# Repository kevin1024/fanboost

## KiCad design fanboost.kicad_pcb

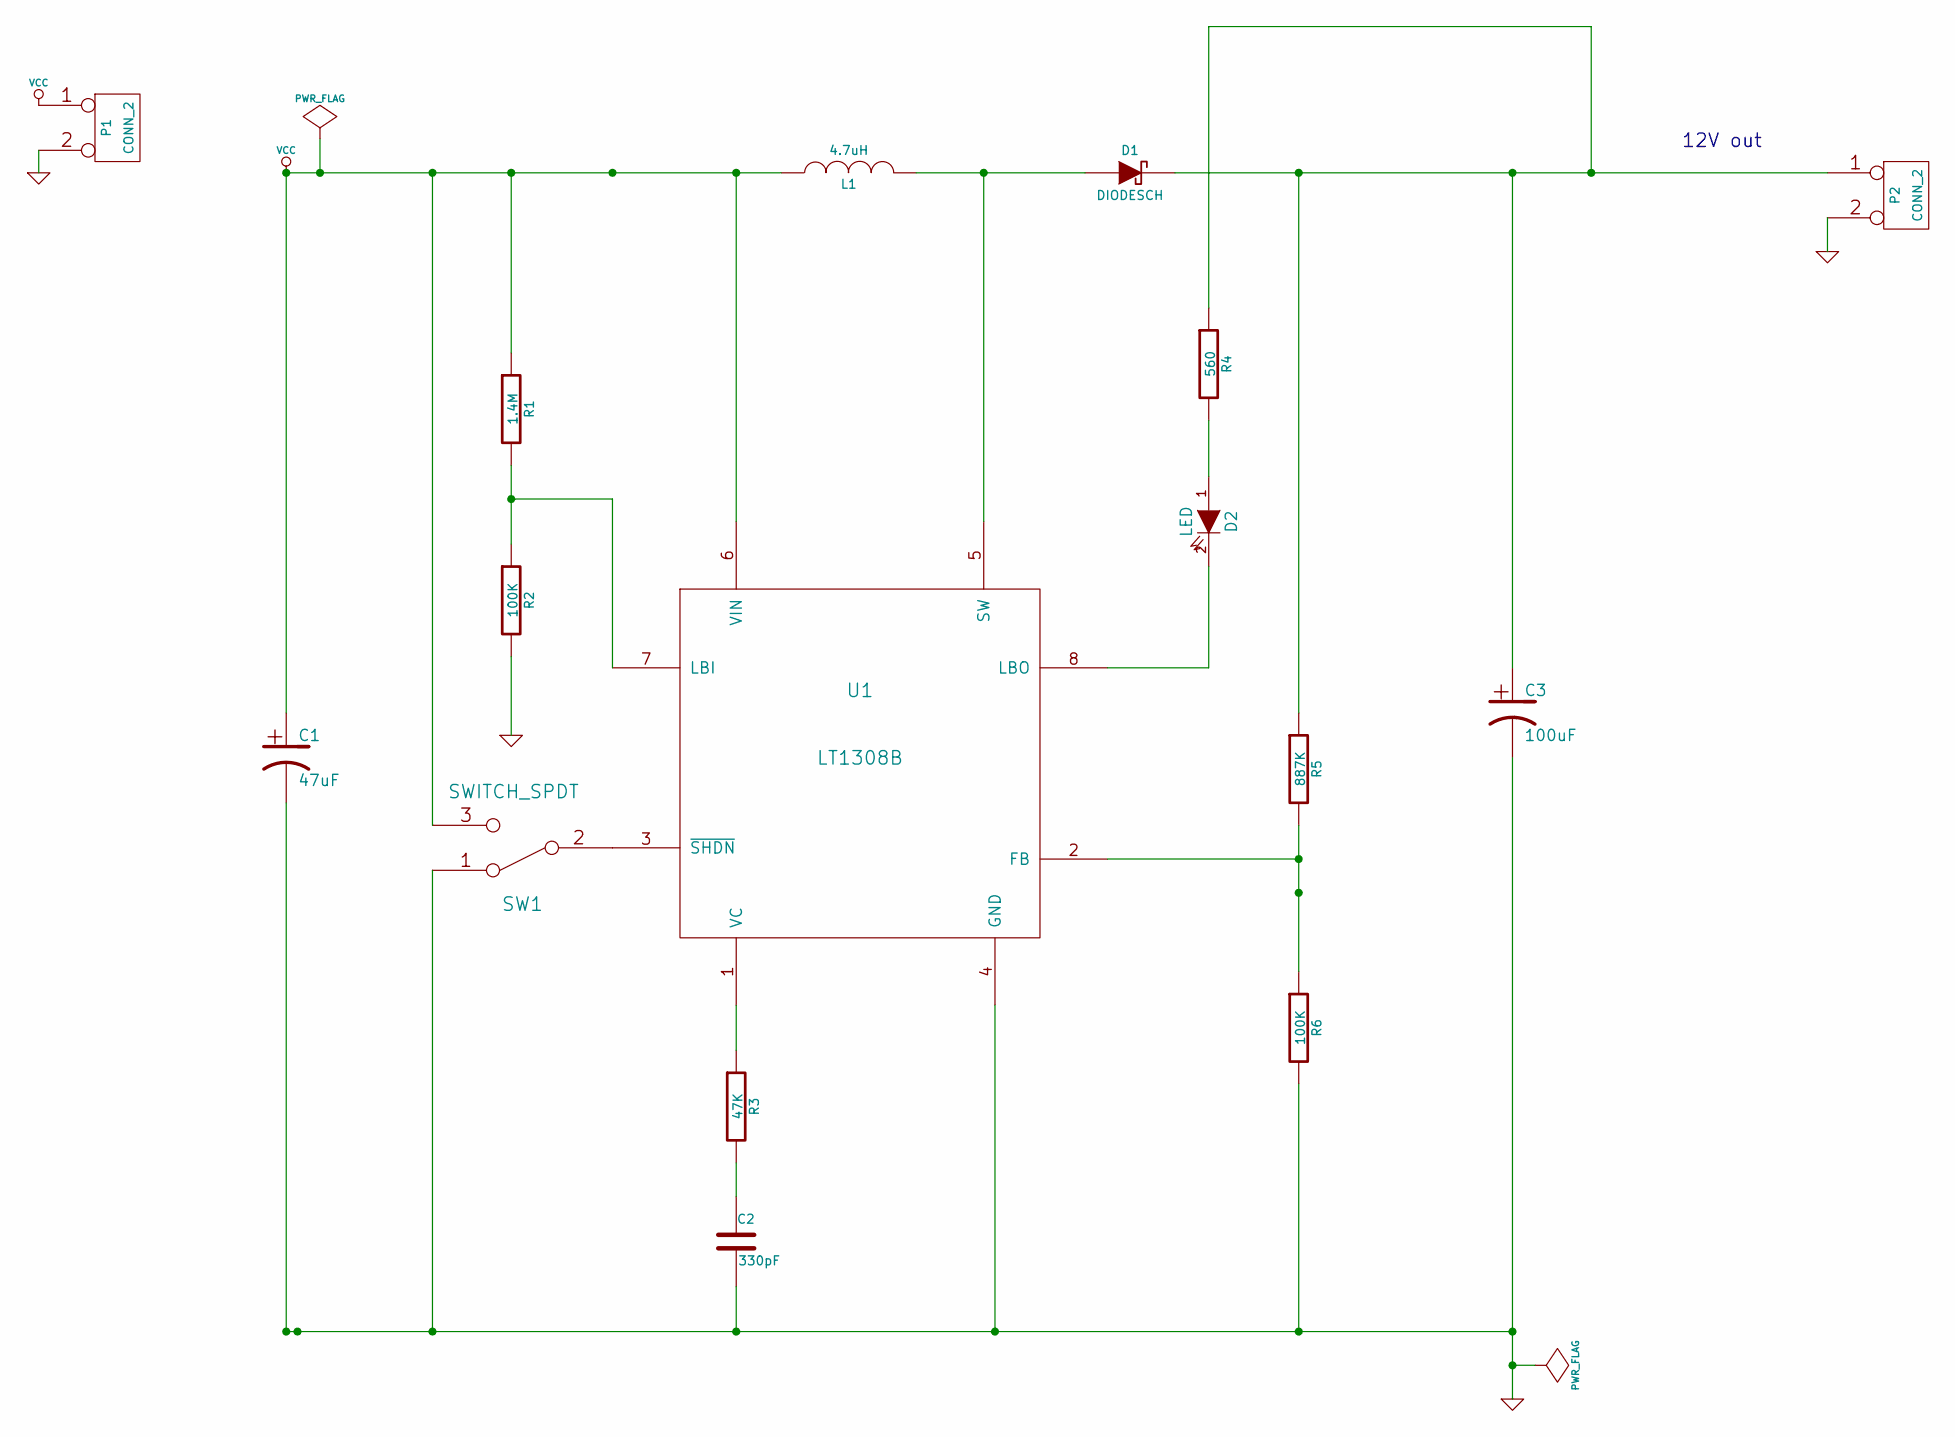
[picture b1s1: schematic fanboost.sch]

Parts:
C1: 47uF
C2: 330pF
C3: 100uF
D1: DIODESCH
D2: LED
L1: 4.7uH
P1, P2: CONN_2
R1: 1.4M
R2, R6: 100K
R3: 47K
R4: 560
R5: 887K
SW1: SWITCH_SPDT
U1: LT1308B

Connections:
GND: C1.2, C2.2, C3.2, P1.2 (PM), P2.2 (PM), R2.2, R6.2, SW1.1, U1.4 (GND)
unnamed: SW1.2, U1.3 (~SHDN)
unnamed: R3.1, U1.1 (VC)
unnamed: D2.1 (A), R4.2
unnamed: C3.1, D1.2 (K), P2.1, R4.1, R5.1
unnamed: R1.2, R2.1, U1.7 (LBI)
unnamed: D2.2 (K), U1.8 (LBO)
unnamed: C2.1, R3.2
unnamed: D1.1 (A), L1.2, U1.5 (SW)
unnamed: R5.2, R6.1, U1.2 (FB)
VCC: C1.1, L1.1, P1.1, R1.1, SW1.3, U1.6 (VIN)

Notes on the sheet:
12V out

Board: 2 copper layers, 16 parts (0 on the bottom side), 11 nets, no tracks yet.

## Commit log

2014-08-27 :neckbeard: Added .gitattributes & .gitignore files
2014-08-27 Add initial schematic
2014-08-27 Plot SVG
2014-08-29 Generate netlist, add ltspice simulation
2014-09-21 Add some footprints
